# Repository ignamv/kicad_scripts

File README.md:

# kicad_scripts
Utility Kicad scripts

## spiral_inductor.py - PCB Spiral Inductor tool

Making RFID readers and tags requires designing antenna inductors.
This tool simplifies the process by allowing you to quickly analyze PCB spiral
inductors with FastHenry to find inductance and Q. Once you're satisfied with a
design, you can save a Kicad footprint to incorporate into your PCB layout.

### Instructions

You can use it online at http://ignamv2.linkpc.net/spiral/

For local use, download the folder rfid_calculator and run cmdline.py. Example:

    $ python3 cmdline.py --help
    usage: cmdline.py [-h] --width WIDTH --height HEIGHT --trace_width TRACE_WIDTH
                      [--mirror] --turns TURNS
                      (--pitch PITCH | --separation SEPARATION) [--zpitch ZPITCH]
                      [--frequency FREQUENCY]
                      [--thickness THICKNESS | --weight WEIGHT] [--fasthenry]
                      [--kicad_mod KICAD_MOD] [--pad_size PAD_SIZE]
                      (--mm | --cm | --mil | --in) [--square | --ellipse]
                      [--vertices_per_turn VERTICES_PER_TURN]

    Calculate PCB spiral inductor with FastHenry and produce Kicad footprint

    optional arguments:
      -h, --help            show this help message and exit
      --width WIDTH         Total outside width
      --height HEIGHT       Total outside height
      --trace_width TRACE_WIDTH
                            Trace width
      --mirror              Reflect footprint horizontally
      --turns TURNS         Number of turns
      --pitch PITCH         Trace pitch (width + separation)
      --separation SEPARATION
                            Separation between traces
      --zpitch ZPITCH       Vertical pitch (default 0 for planar inductor)
      --frequency FREQUENCY
                            Operating frequency
      --thickness THICKNESS
                            Copper thickness
      --weight WEIGHT       Copper weight per unit area in oz/ft²
      --fasthenry           Calculate inductance and Q with FastHenry (
                            http://www.fastfieldsolvers.com )
      --kicad_mod KICAD_MOD
                            Save Kicad footprint to this file
      --pad_size PAD_SIZE   Save Kicad footprint to this file
      --mm                  Dimensions in millimeters
      --cm                  Dimensions in centimeters
      --mil                 Dimensions in mils = 1in / 1000
      --in                  Dimensions in inches
      --square              Generate square spiral
      --ellipse             Generate elliptical spiral
      --vertices_per_turn VERTICES_PER_TURN
                            Number of vertices per turn (for elliptical spirals)

    $ python3 cmdline.py --mm --width=50 --height=25 --pitch=5 --trace_width=2 --turns=3 --fasthenry --kicad_mod=/tmp/ant.kicad_mod --frequency=125e3
    Analysis of 50.0 mm x 25.0 mm 3-turn 5.0 mm pitch 2.0 mm trace inductor at 125.0 kHz

              Inductance: 11.9 nH
    Resonant capacitance: 136.8 µF
                       Q: 5.4e+02

    Footprint written to /tmp/ant.kicad_mod

## place_footprints.py

When you first start pcbnew and read a netlist,
all components are piled up in one place.
This script takes the schematic and pcb files 
and moves the footprints to match their placement in the schematic. 
This is a nicer starting point to route your PCB.

### Instructions

You need to have python 2 installed. First, finish the schematic:

Then export the netlist for pcbnew,
and run cvpcb to associate a footprint to each component.
Launch pcbnew and load the netlist and footprint association, then save.
These are standard steps when making PCBs with Kicad, 
you can check out 
[Contextual Electronics](https://contextualelectronics.com/course/kicad-tutorial/) 
for more detailed instructions.

My script takes the pcb file you just saved
and moves the footprints to match the schematic.
You need to [download the script](place_footprints.py?raw=true) 
to your project directory.
To run it, just drag the project file (.pro) or project folder into the script icon.
Your pcb file now has placed components.

Here's the output from the schematic above:

If you want to see detailed script output (for troubleshooting),
open a terminal (in Windows, use Start -> Run -> cmd.exe)
and go to your project directory

    $ cd %USERPROFILE%\My Documents\example_project
    $ python place_footprints.py .
    Found project ./example_project
    Found schematic: ././example_project.sch
    Found pcb: ././example_project.kicad_pcb
    13:06:04: Debug: Skipping general section token 'links' 
    13:06:04: Debug: Skipping general section token 'area' 
    13:06:04: Debug: Skipping general section token 'drawings' 
    13:06:04: Debug: Skipping general section token 'tracks' 
    13:06:04: Debug: Skipping general section token 'zones' 
    13:06:04: Debug: Skipping general section token 'symbol' 
    Moving module...R1 R2 Q1 R4 C2 R3 C1 P1 P3 P2 
    Backing up ././example_project.kicad_pcb to ././example_project.kicad_pcb.bak6

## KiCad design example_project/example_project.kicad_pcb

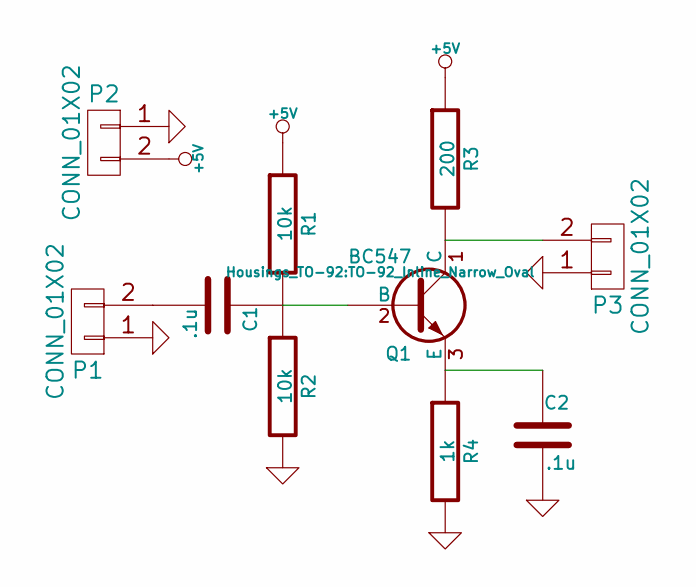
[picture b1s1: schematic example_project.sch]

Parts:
C1, C2: .1u; C_0805_HandSoldering
P1, P2, P3: CONN_01X02; Pin_Header_Angled_1x02
Q1: BC547; TO-92_Inline_Narrow_Oval
R1, R2: 10k; R_0805_HandSoldering
R3: 200; R_0805_HandSoldering
R4: 1k; R_0805_HandSoldering

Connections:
+5V: P2.2, R1.1, R3.1
GND: C2.2, P1.1, P2.1, P3.1, R2.2, R4.2
unnamed: C1.1, Q1.2 (B), R1.2, R2.1
unnamed: C1.2, P1.2
unnamed: C2.1, Q1.3 (E), R4.1
unnamed: P3.2, Q1.1 (C), R3.2

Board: 2 copper layers, 10 parts (0 on the bottom side), 6 nets, no tracks yet.

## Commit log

2015-09-03 Add place_footprints.py
2015-09-04 Improved user friendliness
    Script automatically finds schematic and pcb files
2015-09-22 Add spiral inductor tool
    It analyzes spiral PCB inductors with FastHenry and produces kicad footprints.
2015-09-24 Add option to mirror spiral inductor
2015-10-04 Remove numpy and pint, add web interface
    Removed dependency on numpy and pint
    Added a web interface with flask (can be run locally from calculate.py)
2015-10-05 Add command line support for elliptical spirals
2015-11-01 Add InputFile class for building Fasthenry input files
2015-12-26 Update README.md instructions for spiral calculator
2015-12-26 Look for fasthenry in PATH unless running as webapp
2015-12-29 Rename spiral to square_spiral
2015-12-29 Add javascript to version control
